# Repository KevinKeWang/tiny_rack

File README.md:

# tiny_rack
This is a V2 version of tiny_rack. With the release of the BambuLab H2D it's easy to print larger models. So I updated the eurorack case model for the 6U52HP, and the power board circuit for a more convenient and easy to use design. This version is closer to the aluminum eurorack case I sell. they are exactly the same in power and functionality. Now you can print your own 6U52hp eurorack case in any color you like!

**(tiny_rack v2)**

The first version is smaller and fits most 3D printers. If your printer cannot build such a large part, please browse the V1 version here: https://github.com/KevinKeWang/tiny_rack/tree/V1

**(tiny_rack v1)**

## Main features:

* One-piece 3D printed, no splicing, no metal rails required.
* Maximum current: +12V 2000mA, -12V 1000mA, +5V not available.
* Full load tested.
* The +12V and -12V output ripple is less than 100mV under all load conditions.
* Fully test powered by ZITAY D-Tap to DC(5.5 * 2.1 mm) Cable

## Portable scene using V-mount battery power supply
**Please note that the dtap output voltage should not be lower than 14.2V**
|  |  |
|------------------------------------------------|------------------------------------------------|

## Instructions
The main reason I started this project was the difficulty in finding a simple power bank solution when I was just starting out with DIY modulars. Most of the solutions required specialized rails. needed to control the precision otherwise the modulars would be difficult to install. there were many power board solutions but I couldn't be sure about the quality of their output. Some switching power supplies cause digital modulars to fail to boot.

This series contains the complete series of racks. and a power board with a decent quality of output. The racks is built entirely using 3D printing. one piece (including the rails) and simple to print. the screw holes are not threaded and need to be force screwed in using M3 screws to create the threads. this sacrifices the strength of the racks somewhat. but again makes the build very simple and ready to use straight after printing.

The power supply uses the original 7812/7912 LDO scheme. which is simple and reliable. and I've tested the ripple on the +/-12V rails to under 100mV under all load conditions. You can check the test report. it's not a perfect solution at the moment. but you can see exactly what kind of standards it can achieve.

**I no longer provide 5V in the power supply since most modulars that use 5V can be switched to convert 5V from 12V**

## 3D Print Instructions
* Be sure to place the model vertically, otherwise the dimensions will be off after printing, resulting in the modular not being installed.
* I have provided BambuStudio project files that can be used as a reference for the support structure. gcode files can be used directly for printing.
* Because different brands or different diameters of nozzles may produce different results when printing small circular holes. I made a screw hole diameter test model here. It is recommended to use this model to test before printing the modular case, and select the appropriate screw hole diameter to modify the plasticity source file. When I use the BambuLab H2D printer with a 0.4mm nozzle, a 2.5mm screw hole is the best size. If you use the same printer as me, you can directly use my gcode file for printing.

## Schematics and PCB

**Core PCB front side**

**Core PCB back side**

**How to connect two PCBs**

## Bill of materials (Core PCB)
| Designator                   | Qty | Value              | Footprint     | Description                    | Ref. Mouser                          | Ref. LCSC | References                            |
|------------------------------|-----|--------------------|---------------|--------------------------------|--------------------------------------|-----------|---------------------------------------|
| **SMT parts**                |     |                    |               |                                |                                      |           |                                       |
| LED1, LED2, LED3, LED4       | 4   | LED                | 0805          | LED                            | 638-1215UYCS530A28                   | C2987021  | EVERLIGHT 17-215/GHC-YP1Q2B16Y/3T     |
| R1, R2, R3, R5, R6, R10, R4  | 7   | 2.4k               | 0805          | Resistor                       | 667-ERJ-6ENF2401V                    | C17526    | UNI-ROYAL 0805W8F2401T5E              |
| R7, R8, R9                   | 3   | 510R               | 0805          | Resistor (Optional)            | 667-ERJ-6ENF5100V                    | C17734    | UNI-ROYAL 0805W8F5100T5E              |
| C4, C9                       | 2   | 100nF              | CASE-A-3216   | tantalum                       | 581-TAJA104K035                      | C7173     | Kyocera AVX TAJA104K035RNJ            |
| C3, C8                       | 2   | 330nF              | CASE-A-3216   | tantalum                       | 581-TAJA334K035                      | C8014     | Kyocera AVX TAJA334K035RNJ            |
| C11                          | 1   | 1uF                | CASE-A-3216   | tantalum                       | 581-TAJA105K035R                     | C7176     | Kyocera AVX TAJA105K035RNJ            |
| C10                          | 1   | 2.2uF              | CASE-B-3528   | tantalum                       | 581-TAJB225K035                      | C19276    | Kyocera AVX TAJB225K035RNJ            |
| D1, D2, D3                   | 3   | DIODE              | SMA(DO-214AC) | DIODE                          | 621-B360A-F                          | C94193    | DIODES B360A-13-F                     |
| **PTH parts**                |     |                    |               |                                |                                      |           |                                       |
| C2                           | 1   | 22uF               | D6.3xL7mm     | Electrolytic                   | 647-UKL1V220KEDANA                   | C433313   | Nichicon USV1V220MFD                  |
| C1                           | 1   | 120uF              | D8xL7mm       | Electrolytic                   | 667-50SEK120M                        | C3010233  | PANASONIC 50SEK120M                   |
| KK1, KK3, KK4                | 3   | Heat sink          |               | Heat sink                      | 532-529702B25G                       | C286227   | Heat sink                             |
| J1                           | 1   | DC Power Connector |               | 2.1 mm, 5.5 mm                 | 710-694106301002                     | C136744   | Wurth Elektronik 694106301002         |
| J2, J6                       | 2   | M3 screw terminal  |               | terminal (Optional)            | 534-7770                             | C481448   | Keystone 7770                         |
| **Adapter**                  |     |                    |               |                                |                                      |           |                                       |
| 15V Adapter                  | 1   | 15V Adapter        |               | GST60A15-P1J                   | 709-GST60A15-P1J                     | -         | MEANWELL 15V DC Adapter               |

**It is recommended to use the adapter model I have tested.**

## Bill of materials (EXP PCB)
| Designator                   | Qty | Value              | Footprint     | Description                    | Ref. Mouser                          | Ref. LCSC | References                            |
|------------------------------|-----|--------------------|---------------|--------------------------------|--------------------------------------|-----------|---------------------------------------|
| **SMT parts**                |     |                    |               |                                |                                      |           |                                       |
| J1, J2, J6, J7, J8, J9, J11, J12, J13, J14, J15, J16, J17, J18, J19, J20, J21, J22, J23, J24, J25, J26, J27, J28, J29, J30, J31, J32, J33, J34 | 30   | 2x8 header         | 2.54mm pitch  | 2x8 header                     | 710-61231620621                      | C2685064   | 2x8 male header, 2.54mm pitch         |
| J3, J4, J5, J10              | 4   | 2x3 header         | 2.54mm pitch  | 2x3 header                     | 710-61300621121                      | C358692   | 2x3 male header, 2.54mm pitch         |

## Mechanical assembly

**There is no circuit on the back of the expansion board, so it can be directly attached to any surface with tape.**

## Software

3D Modeling Software: plasticity

https://www.plasticity.xyz/

PCB Software: eagle

https://www.autodesk.com/products/eagle/overview

## Test Report
Test equipment:
* Gwinstek GPP-3323 DC Power Supply (as an electronic load) **for +12V -12V**
* Itech IT8500G+ DC Electronic Load **for +5V**
* Rigol MSO5000 Oscilloscopes **for ripple measurement**
* Software for automated testing
Test methods:
Each channel is cycled from 0mA to maximum load, 50mA in one step, to test all combinations of loads and output a CSV file.

**There are some power supply solutions that can generate large ripple or even fail in specific load scenarios, such as when the gap between positive and negative rail loads is too large. That's why my tests cover all load scenarios.**

## License
**The tiny_rack v2 project is made available under a CC-BY-NC-SA-3.0 license.**

If you want to make a few cases for your own use, go ahead and make them. If you're a synth studio and want to use them for product testing/demonstration etc, that's also welcome as long as it doesn't involve selling these case directly. **Please do not make and sell these case in bulk.**

## Links
Official website:  https://bitiworkshop.com/

Purchase here: https://store.bitiworkshop.com/

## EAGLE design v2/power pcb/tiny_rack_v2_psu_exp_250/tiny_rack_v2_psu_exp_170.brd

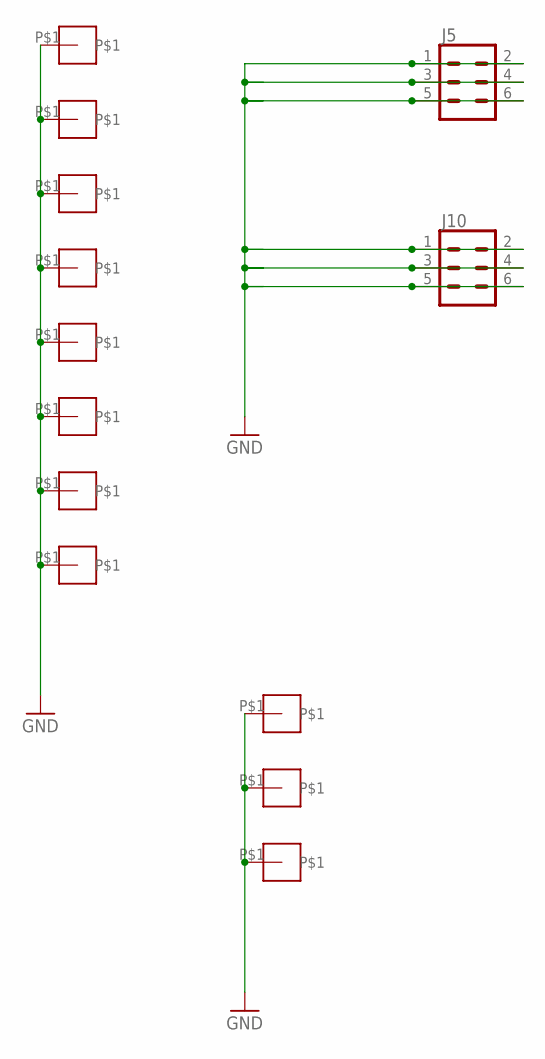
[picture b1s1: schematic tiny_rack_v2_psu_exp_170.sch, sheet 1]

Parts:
J5, J10: CONN_03X2FEMALE_SMD; 2X3_SMD
U$1, U$2, U$3, U$4, U$5, U$6, U$8, U$9, U$10, U$11, U$12: M3-HOLE

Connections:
GND: J5.1, J5.2, J5.3, J5.4, J5.5, J5.6, J10.1, J10.2, J10.3, J10.4, J10.5, J10.6, U$1.P$1, U$2.P$1, U$3.P$1, U$4.P$1, U$5.P$1, U$6.P$1, U$8.P$1, U$9.P$1, U$10.P$1, U$11.P$1, U$12.P$1; also elsewhere on the board

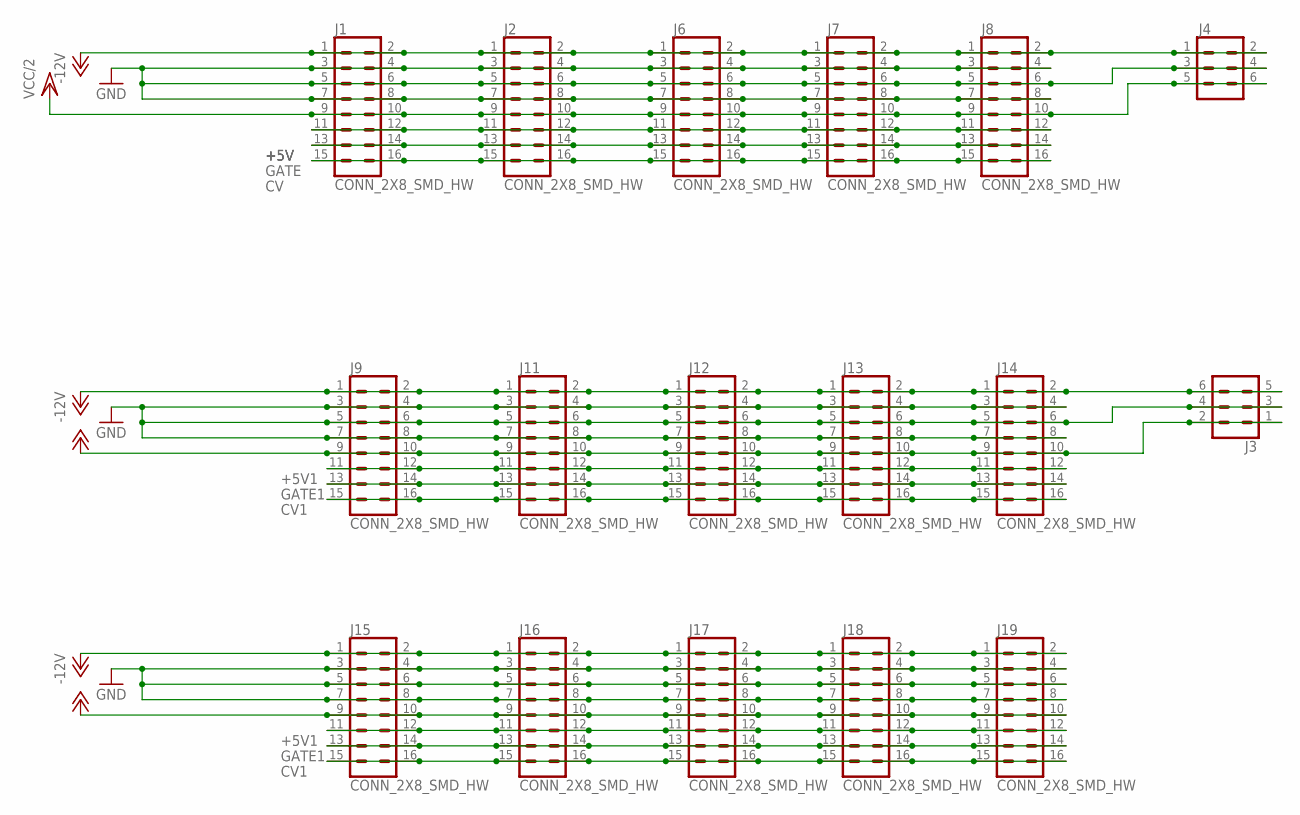
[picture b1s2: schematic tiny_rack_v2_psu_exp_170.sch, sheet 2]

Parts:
J1, J2, J6, J7, J8, J9, J11, J12, J13, J14, J15, J16, J17, J18, J19: CONN_2X8_SMD_HW; 2X8-SHROUDED_SMD_HW
J3, J4: CONN_03X2FEMALE_SMD; 2X3_SMD

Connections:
+5V: J1.11, J1.12, J2.11, J2.12, J6.11, J6.12, J7.11, J7.12, J8.11, J8.12; also elsewhere on the board
+5V1: J9.11, J9.12, J11.11, J11.12, J12.11, J12.12, J13.11, J13.12, J14.11, J14.12, J15.11, J15.12, J16.11, J16.12, J17.11, J17.12, J18.11, J18.12, J19.11, J19.12; also elsewhere on the board
+12V: J3.1, J3.2, J9.9, J9.10, J11.9, J11.10, J12.9, J12.10, J13.9, J13.10, J14.9, J14.10, J15.9, J15.10, J16.9, J16.10, J17.9, J17.10, J18.9, J18.10, J19.9, J19.10; also elsewhere on the board
-12V: J1.1, J1.2, J2.1, J2.2, J3.5, J3.6, J4.1, J4.2, J6.1, J6.2, J7.1, J7.2, J8.1, J8.2, J9.1, J9.2, J11.1, J11.2, J12.1, J12.2, J13.1, J13.2, J14.1, J14.2, J15.1, J15.2, J16.1, J16.2, J17.1, J17.2, J18.1, J18.2, J19.1, J19.2; also elsewhere on the board
CV: J1.15, J1.16, J2.15, J2.16, J6.15, J6.16, J7.15, J7.16, J8.15, J8.16; also elsewhere on the board
CV1: J9.15, J9.16, J11.15, J11.16, J12.15, J12.16, J13.15, J13.16, J14.15, J14.16, J15.15, J15.16, J16.15, J16.16, J17.15, J17.16, J18.15, J18.16, J19.15, J19.16; also elsewhere on the board
GATE: J1.13, J1.14, J2.13, J2.14, J6.13, J6.14, J7.13, J7.14, J8.13, J8.14; also elsewhere on the board
GATE1: J9.13, J9.14, J11.13, J11.14, J12.13, J12.14, J13.13, J13.14, J14.13, J14.14, J15.13, J15.14, J16.13, J16.14, J17.13, J17.14, J18.13, J18.14, J19.13, J19.14; also elsewhere on the board
GND: J1.3, J1.4, J1.5, J1.6, J1.7, J1.8, J2.3, J2.4, J2.5, J2.6, J2.7, J2.8, J3.3, J3.4, J4.3, J4.4, J6.3, J6.4, J6.5, J6.6, J6.7, J6.8, J7.3, J7.4, J7.5, J7.6, J7.7, J7.8, J8.3, J8.4, J8.5, J8.6, J8.7, J8.8, J9.3, J9.4, J9.5, J9.6, J9.7, J9.8, J11.3, J11.4, J11.5, J11.6, J11.7, J11.8, J12.3, J12.4, J12.5, J12.6, J12.7, J12.8, J13.3, J13.4, J13.5, J13.6, J13.7, J13.8, J14.3, J14.4, J14.5, J14.6, J14.7, J14.8, J15.3, J15.4, J15.5, J15.6, J15.7, J15.8, J16.3, J16.4, J16.5, J16.6, J16.7, J16.8, J17.3, J17.4, J17.5, J17.6, J17.7, J17.8, J18.3, J18.4, J18.5, J18.6, J18.7, J18.8, J19.3, J19.4, J19.5, J19.6, J19.7, J19.8; also elsewhere on the board
VCC/2: J1.9, J1.10, J2.9, J2.10, J4.5, J4.6, J6.9, J6.10, J7.9, J7.10, J8.9, J8.10; also elsewhere on the board

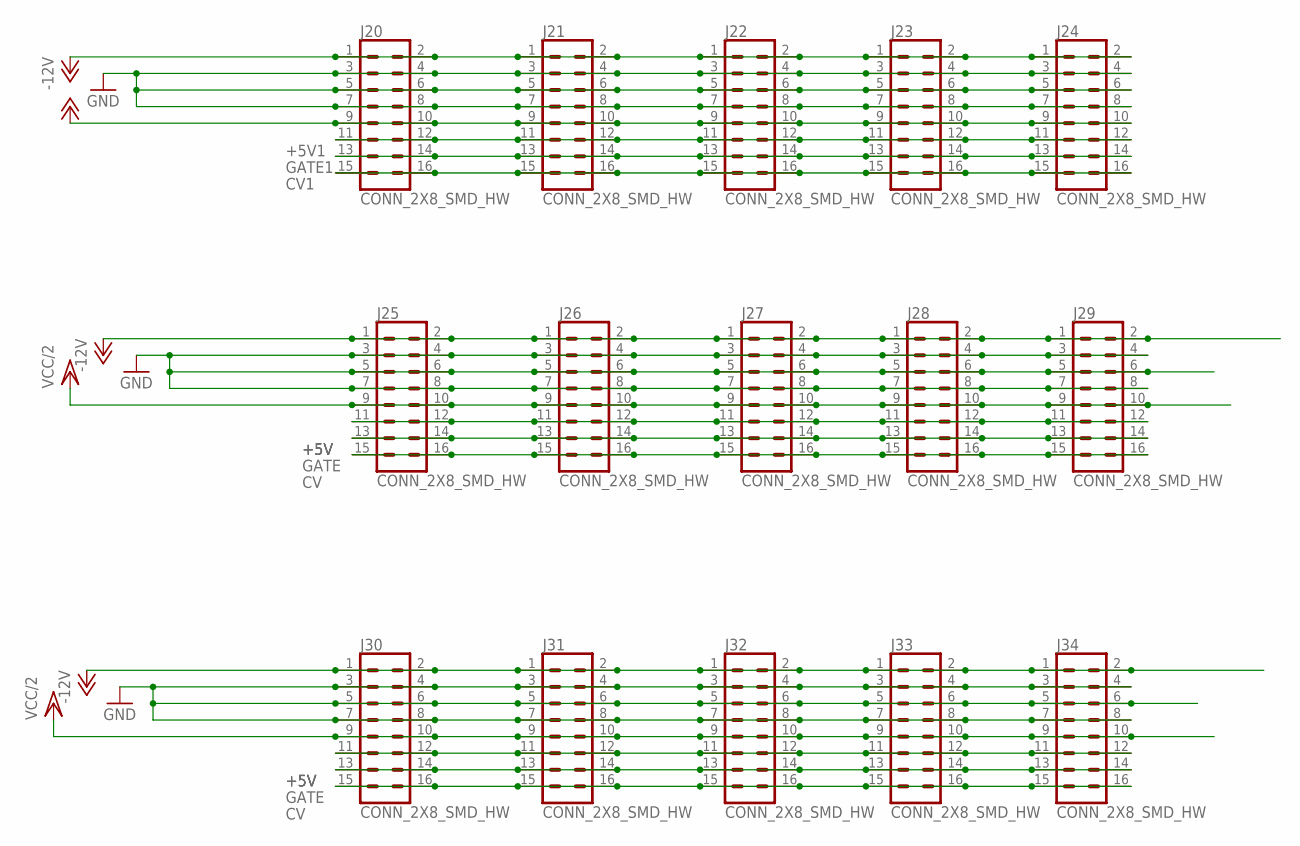
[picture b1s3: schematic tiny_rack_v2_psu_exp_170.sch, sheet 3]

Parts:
J20, J21, J22, J23, J24, J25, J26, J27, J28, J29, J30, J31, J32, J33, J34: CONN_2X8_SMD_HW; 2X8-SHROUDED_SMD_HW

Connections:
+5V: J25.11, J25.12, J26.11, J26.12, J27.11, J27.12, J28.11, J28.12, J29.11, J29.12, J30.11, J30.12, J31.11, J31.12, J32.11, J32.12, J33.11, J33.12, J34.11, J34.12; also elsewhere on the board
+5V1: J20.11, J20.12, J21.11, J21.12, J22.11, J22.12, J23.11, J23.12, J24.11, J24.12; also elsewhere on the board
+12V: J20.9, J20.10, J21.9, J21.10, J22.9, J22.10, J23.9, J23.10, J24.9, J24.10; also elsewhere on the board
-12V: J20.1, J20.2, J21.1, J21.2, J22.1, J22.2, J23.1, J23.2, J24.1, J24.2, J25.1, J25.2, J26.1, J26.2, J27.1, J27.2, J28.1, J28.2, J29.1, J29.2, J30.1, J30.2, J31.1, J31.2, J32.1, J32.2, J33.1, J33.2, J34.1, J34.2; also elsewhere on the board
CV: J25.15, J25.16, J26.15, J26.16, J27.15, J27.16, J28.15, J28.16, J29.15, J29.16, J30.15, J30.16, J31.15, J31.16, J32.15, J32.16, J33.15, J33.16, J34.15, J34.16; also elsewhere on the board
CV1: J20.15, J20.16, J21.15, J21.16, J22.15, J22.16, J23.15, J23.16, J24.15, J24.16; also elsewhere on the board
GATE: J25.13, J25.14, J26.13, J26.14, J27.13, J27.14, J28.13, J28.14, J29.13, J29.14, J30.13, J30.14, J31.13, J31.14, J32.13, J32.14, J33.13, J33.14, J34.13, J34.14; also elsewhere on the board
GATE1: J20.13, J20.14, J21.13, J21.14, J22.13, J22.14, J23.13, J23.14, J24.13, J24.14; also elsewhere on the board
GND: J20.3, J20.4, J20.5, J20.6, J20.7, J20.8, J21.3, J21.4, J21.5, J21.6, J21.7, J21.8, J22.3, J22.4, J22.5, J22.6, J22.7, J22.8, J23.3, J23.4, J23.5, J23.6, J23.7, J23.8, J24.3, J24.4, J24.5, J24.6, J24.7, J24.8, J25.3, J25.4, J25.5, J25.6, J25.7, J25.8, J26.3, J26.4, J26.5, J26.6, J26.7, J26.8, J27.3, J27.4, J27.5, J27.6, J27.7, J27.8, J28.3, J28.4, J28.5, J28.6, J28.7, J28.8, J29.3, J29.4, J29.5, J29.6, J29.7, J29.8, J30.3, J30.4, J30.5, J30.6, J30.7, J30.8, J31.3, J31.4, J31.5, J31.6, J31.7, J31.8, J32.3, J32.4, J32.5, J32.6, J32.7, J32.8, J33.3, J33.4, J33.5, J33.6, J33.7, J33.8, J34.3, J34.4, J34.5, J34.6, J34.7, J34.8; also elsewhere on the board
VCC/2: J25.9, J25.10, J26.9, J26.10, J27.9, J27.10, J28.9, J28.10, J29.9, J29.10, J30.9, J30.10, J31.9, J31.10, J32.9, J32.10, J33.9, J33.10, J34.9, J34.10; also elsewhere on the board

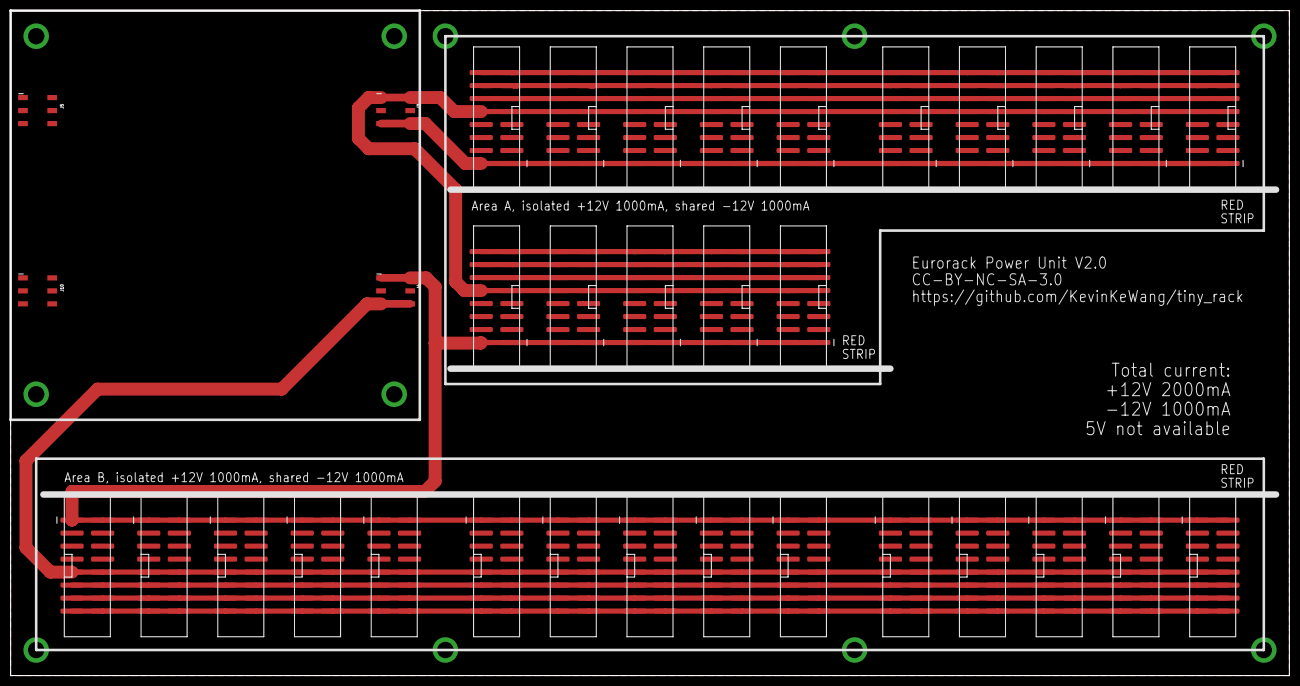
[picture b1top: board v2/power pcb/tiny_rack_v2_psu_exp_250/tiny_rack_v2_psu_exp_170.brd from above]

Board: 4 copper layers, 250.0 x 130.0 mm, 45 parts (0 on the bottom side), 10 nets.

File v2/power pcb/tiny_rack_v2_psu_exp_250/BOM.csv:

Designator,Comment,Footprint,JLC PartNo.
"J3, J4, J5, J10",2X3PIN,SMT,C780054
"J1, J2, J6, J7, J8, J9, J11, J12, J13, J14, J15, J16, J17, J18, J19, J20, J21, J22, J23, J24, J25, J26, J27, J28, J29, J30, J31, J32, J33, J34",2X8PIN,SMT,C2685064

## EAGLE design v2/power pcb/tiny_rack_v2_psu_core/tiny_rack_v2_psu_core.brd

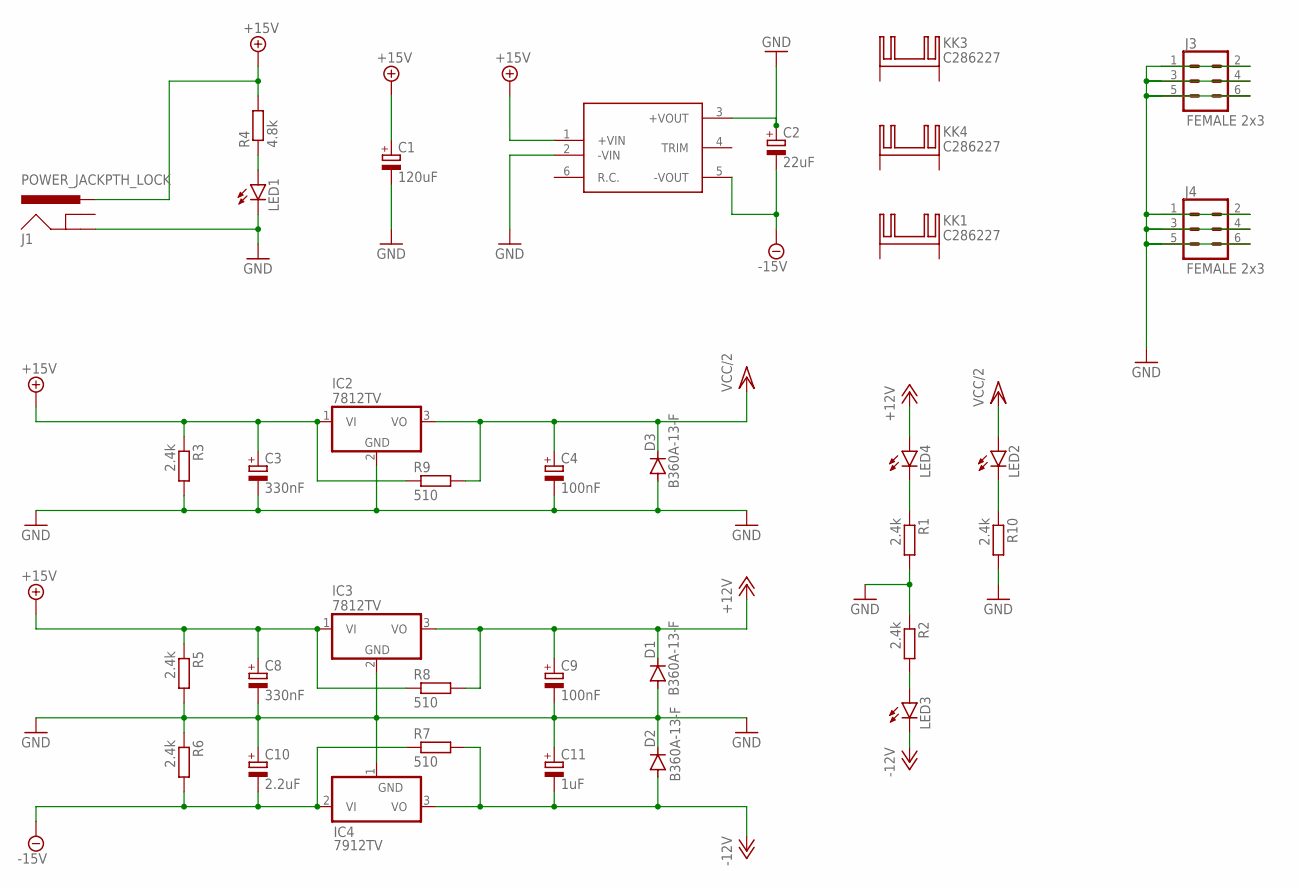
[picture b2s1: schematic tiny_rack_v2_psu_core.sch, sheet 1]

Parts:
C1: 120uF; E5-10,5
C2: 22uF; E2,5-6
C3, C8: 330nF; CAPMP3216X180N
C4, C9: 100nF; CAPMP3216X180N
C10: 2.2uF; CAPMP3528X210N
C11: 1uF; CAPMP3216X180N
D1, D2, D3: B360A-13-F; DO-214AC
IC1: SKMW
IC2, IC3: 7812TV; TO220V
IC4: 7912TV; TO220V
J1: POWER_JACKPTH_LOCK; POWER_JACK_PTH_LOCK
J3, J4: FEMALE 2x3; 2X3
KK1, KK3, KK4: C286227
LED1, LED2, LED3, LED4: LEDCHIP-LED0805; CHIP-LED0805
R1, R2, R3, R5, R6, R10: 2.4k; R0805
R4: 4.8k; R0805
R7, R8, R9: 510; R0805

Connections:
+12V: C9.1 (+), D1.C, IC3.3 (VO), LED4.A, R8.2; also elsewhere on the board
+15V: C1.+, C3.1 (+), C8.1 (+), IC1.1 (+VIN), IC2.1 (VI), IC3.1 (VI), J1.PWR, R3.1, R4.2, R5.1, R8.1, R9.1; also elsewhere on the board
-12V: C11.2 (-), D2.A, IC4.3 (VO), LED3.C, R7.2; also elsewhere on the board
-15V: C2.-, C10.2 (-), IC1.5 (-VOUT), IC4.2 (VI), R6.2, R7.1
GND: C1.-, C2.+, C3.2 (-), C4.2 (-), C8.2 (-), C9.2 (-), C10.1 (+), C11.1 (+), D1.A, D2.C, D3.A, IC1.2 (-VIN), IC1.3 (+VOUT), IC2.2 (GND), IC3.2 (GND), IC4.1 (GND), J1.GND, J3.1, J3.2, J3.3, J3.4, J3.5, J3.6, J4.1, J4.2, J4.3, J4.4, J4.5, J4.6, LED1.C, R1.2, R2.1, R3.2, R5.2, R6.1, R10.2; also elsewhere on the board
unnamed: LED4.C, R1.1
unnamed: LED2.C, R10.1
unnamed: LED3.A, R2.2
unnamed: LED1.A, R4.1
VCC/2: C4.1 (+), D3.C, IC2.3 (VO), LED2.A, R9.2; also elsewhere on the board

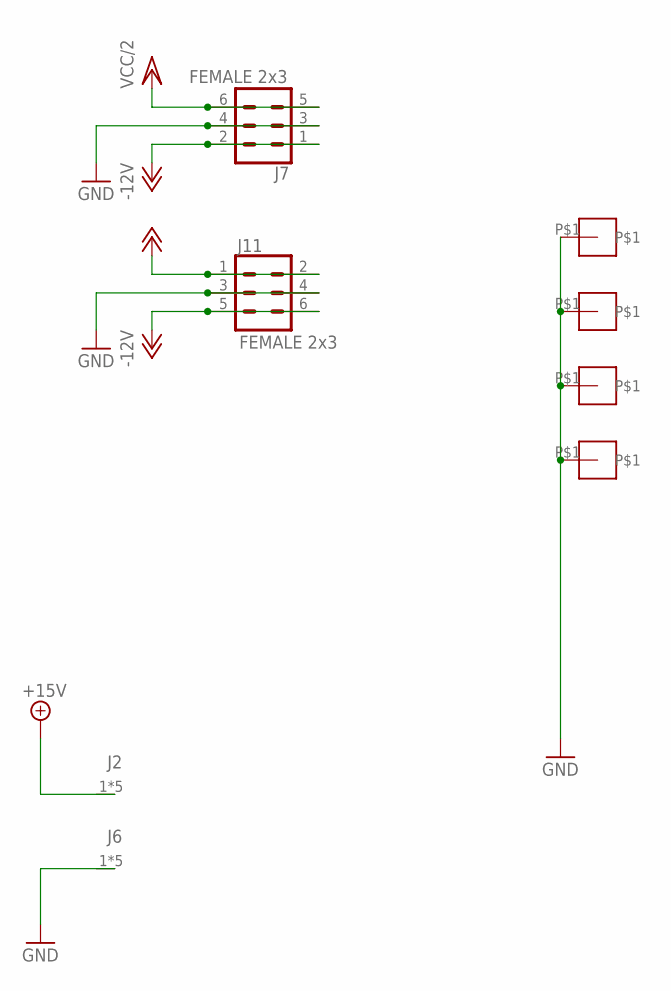
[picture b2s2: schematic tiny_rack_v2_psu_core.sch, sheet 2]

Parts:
J2, J6: 30A-SCREW-CONN; 50X72
J7, J11: FEMALE 2x3; 2X3
U$3, U$4, U$5, U$6: M3-HOLE

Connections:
+12V: J11.1, J11.2; also elsewhere on the board
+15V: J2.1, J2.2, J2.3, J2.4, J2.P$1; also elsewhere on the board
-12V: J7.1, J7.2, J11.5, J11.6; also elsewhere on the board
GND: J6.1, J6.2, J6.3, J6.4, J6.P$1, J7.3, J7.4, J11.3, J11.4, U$3.P$1, U$4.P$1, U$5.P$1, U$6.P$1; also elsewhere on the board
VCC/2: J7.5, J7.6; also elsewhere on the board

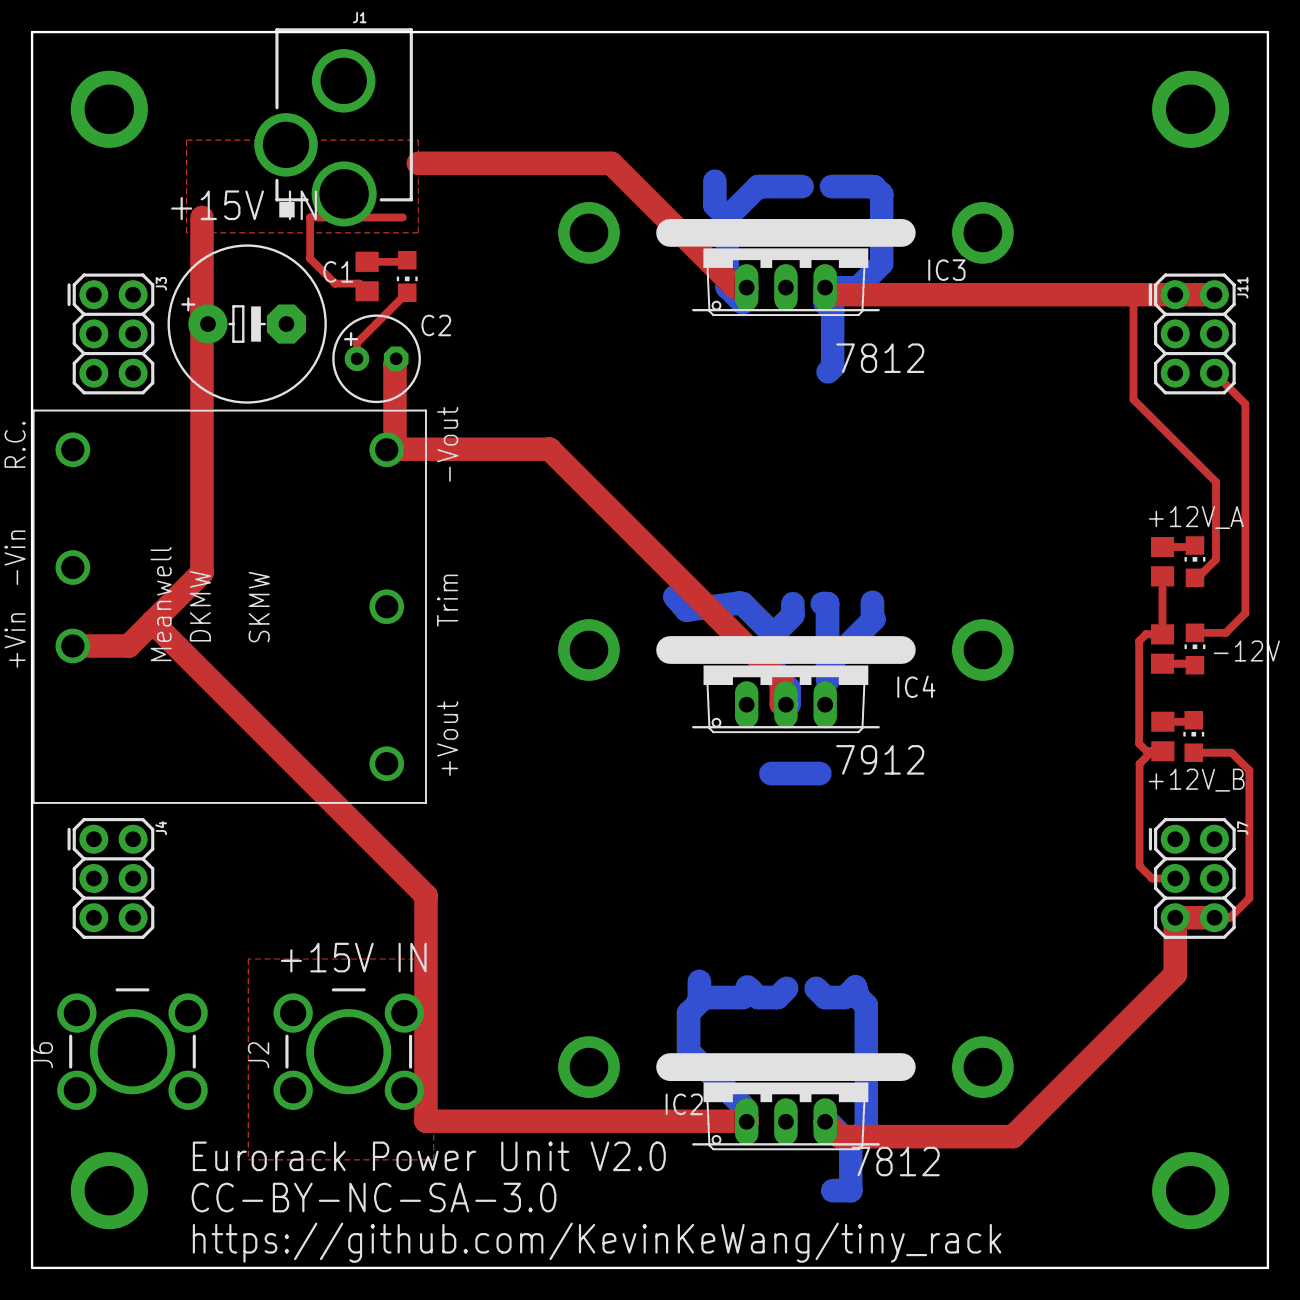
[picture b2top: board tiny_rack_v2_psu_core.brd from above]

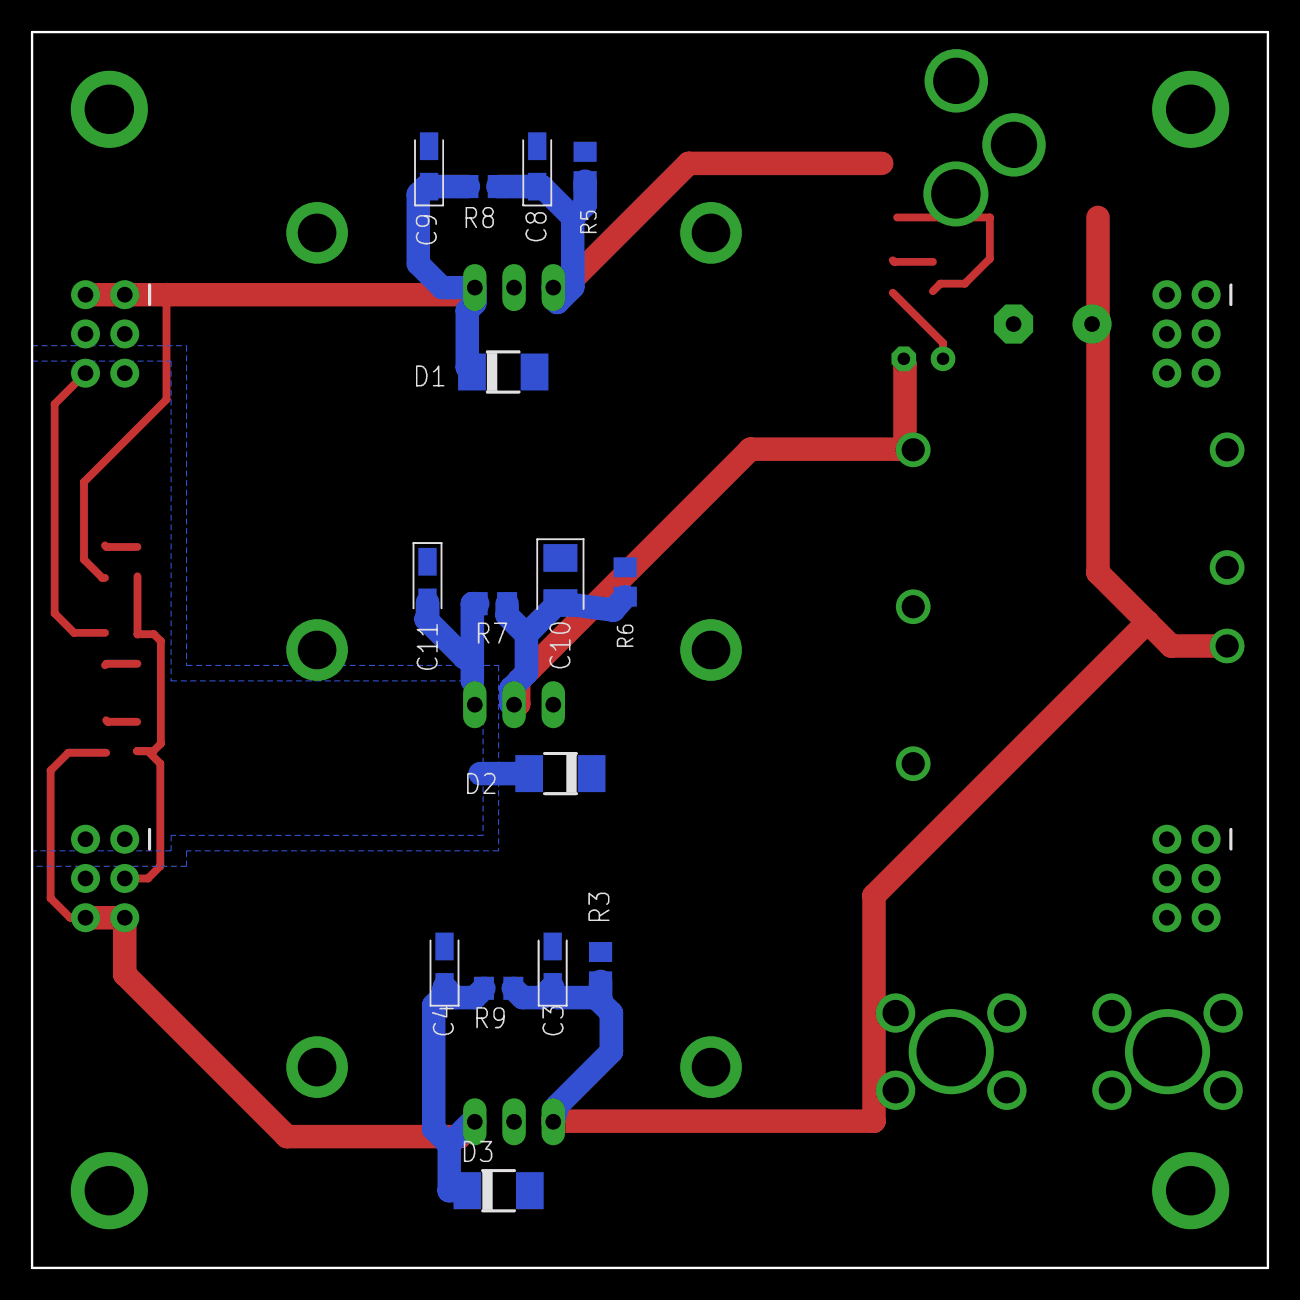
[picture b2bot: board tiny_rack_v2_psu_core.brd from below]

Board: 4 copper layers, 80.0 x 80.0 mm, 43 parts (15 on the bottom side), 10 nets.

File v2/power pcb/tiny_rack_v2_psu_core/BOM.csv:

Designator,Qty,Comment,Footprint,JLC PartNo.
"LED1, LED2, LED3, LED4",4,LED,0805,C389524
"C4, C9",2,100nF,C7173,C7173
C1,1,120uF,C134861,C134861
C11,1,1uF,C7176,C7176
C10,1,2.2uF,C19276,C19276
"R1, R2, R3, R5, R6, R10, R4",7,2.4k,0805,C17526
C2,1,22uF,C1578600,C1578600
"J2, J6, J8, J9",4,30A-SCREW-CONN,50X72,C481448
"C3, C8",2,330nF,C8014,C8014
"R7, R8, R9",3,510R,0805,C17734
"D1, D2, D3",3,B360A-13-F,DO-214AC,C94193
"KK1, KK3, KK4",3,C286227,C286227,C286227
J1,1,C136744,C136744,C136744

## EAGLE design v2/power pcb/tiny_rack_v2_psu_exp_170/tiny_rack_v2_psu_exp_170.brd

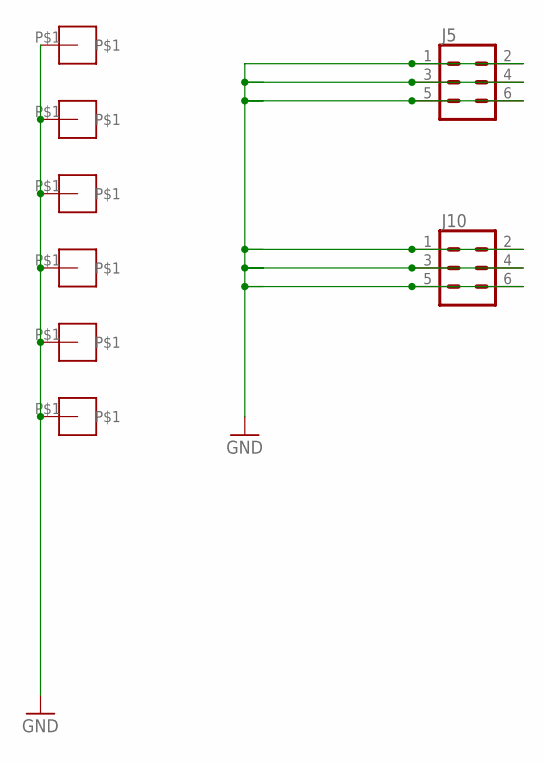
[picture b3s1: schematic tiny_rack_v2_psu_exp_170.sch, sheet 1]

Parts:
J5, J10: CONN_03X2FEMALE_SMD; 2X3_SMD
U$1, U$2, U$3, U$4, U$5, U$6: M3-HOLE

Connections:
GND: J5.1, J5.2, J5.3, J5.4, J5.5, J5.6, J10.1, J10.2, J10.3, J10.4, J10.5, J10.6, U$1.P$1, U$2.P$1, U$3.P$1, U$4.P$1, U$5.P$1, U$6.P$1; also elsewhere on the board

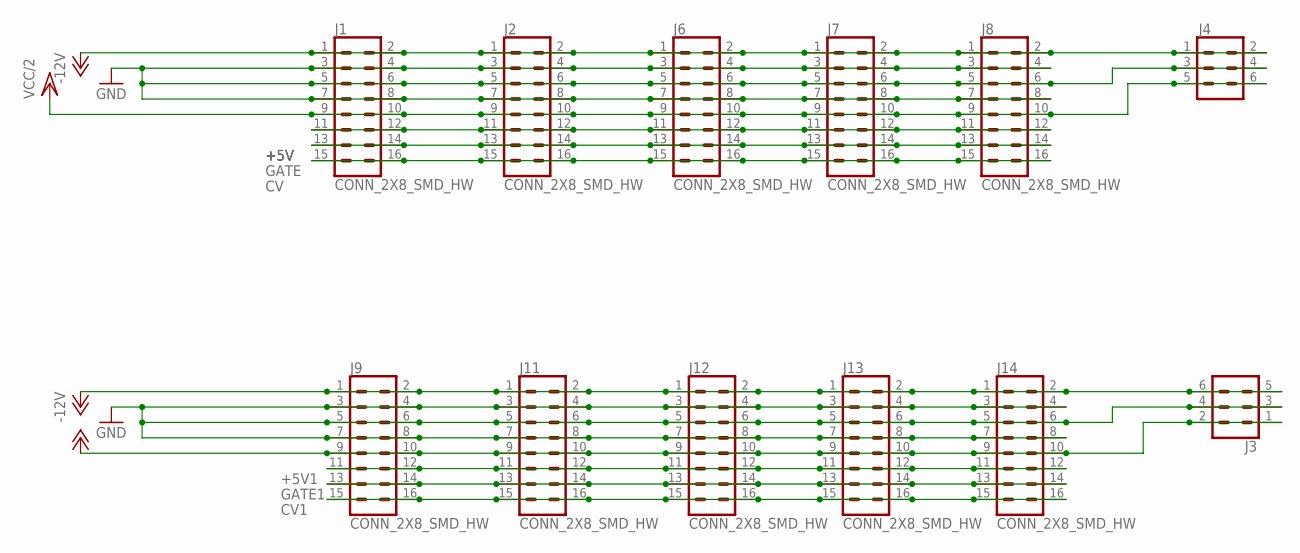
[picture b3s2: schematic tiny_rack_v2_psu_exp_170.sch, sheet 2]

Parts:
J1, J2, J6, J7, J8, J9, J11, J12, J13, J14: CONN_2X8_SMD_HW; 2X8-SHROUDED_SMD_HW
J3, J4: CONN_03X2FEMALE_SMD; 2X3_SMD

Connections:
+5V: J1.11, J1.12, J2.11, J2.12, J6.11, J6.12, J7.11, J7.12, J8.11, J8.12
+5V1: J9.11, J9.12, J11.11, J11.12, J12.11, J12.12, J13.11, J13.12, J14.11, J14.12
+12V: J3.1, J3.2, J9.9, J9.10, J11.9, J11.10, J12.9, J12.10, J13.9, J13.10, J14.9, J14.10
-12V: J1.1, J1.2, J2.1, J2.2, J3.5, J3.6, J4.1, J4.2, J6.1, J6.2, J7.1, J7.2, J8.1, J8.2, J9.1, J9.2, J11.1, J11.2, J12.1, J12.2, J13.1, J13.2, J14.1, J14.2
CV: J1.15, J1.16, J2.15, J2.16, J6.15, J6.16, J7.15, J7.16, J8.15, J8.16
CV1: J9.15, J9.16, J11.15, J11.16, J12.15, J12.16, J13.15, J13.16, J14.15, J14.16
GATE: J1.13, J1.14, J2.13, J2.14, J6.13, J6.14, J7.13, J7.14, J8.13, J8.14
GATE1: J9.13, J9.14, J11.13, J11.14, J12.13, J12.14, J13.13, J13.14, J14.13, J14.14
GND: J1.3, J1.4, J1.5, J1.6, J1.7, J1.8, J2.3, J2.4, J2.5, J2.6, J2.7, J2.8, J3.3, J3.4, J4.3, J4.4, J6.3, J6.4, J6.5, J6.6, J6.7, J6.8, J7.3, J7.4, J7.5, J7.6, J7.7, J7.8, J8.3, J8.4, J8.5, J8.6, J8.7, J8.8, J9.3, J9.4, J9.5, J9.6, J9.7, J9.8, J11.3, J11.4, J11.5, J11.6, J11.7, J11.8, J12.3, J12.4, J12.5, J12.6, J12.7, J12.8, J13.3, J13.4, J13.5, J13.6, J13.7, J13.8, J14.3, J14.4, J14.5, J14.6, J14.7, J14.8; also elsewhere on the board
VCC/2: J1.9, J1.10, J2.9, J2.10, J4.5, J4.6, J6.9, J6.10, J7.9, J7.10, J8.9, J8.10

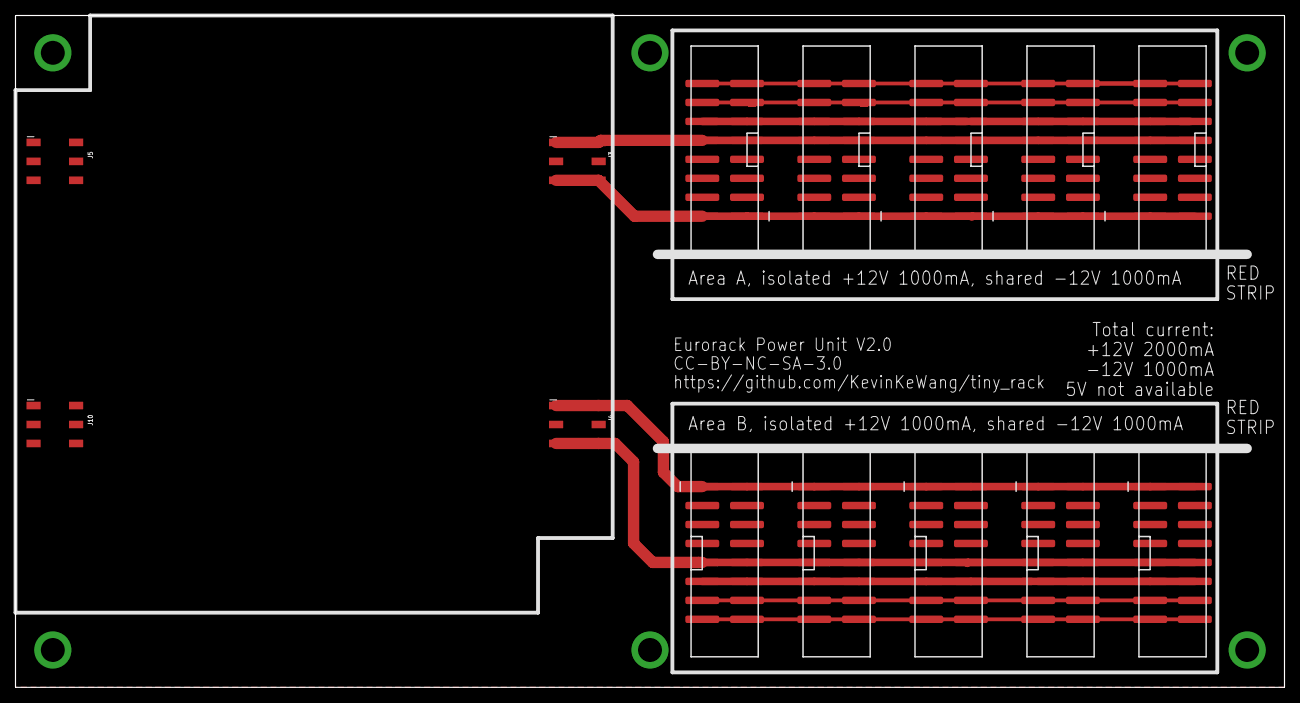
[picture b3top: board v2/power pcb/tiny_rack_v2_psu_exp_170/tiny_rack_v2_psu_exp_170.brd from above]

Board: 4 copper layers, 170.0 x 90.0 mm, 20 parts (0 on the bottom side), 10 nets.

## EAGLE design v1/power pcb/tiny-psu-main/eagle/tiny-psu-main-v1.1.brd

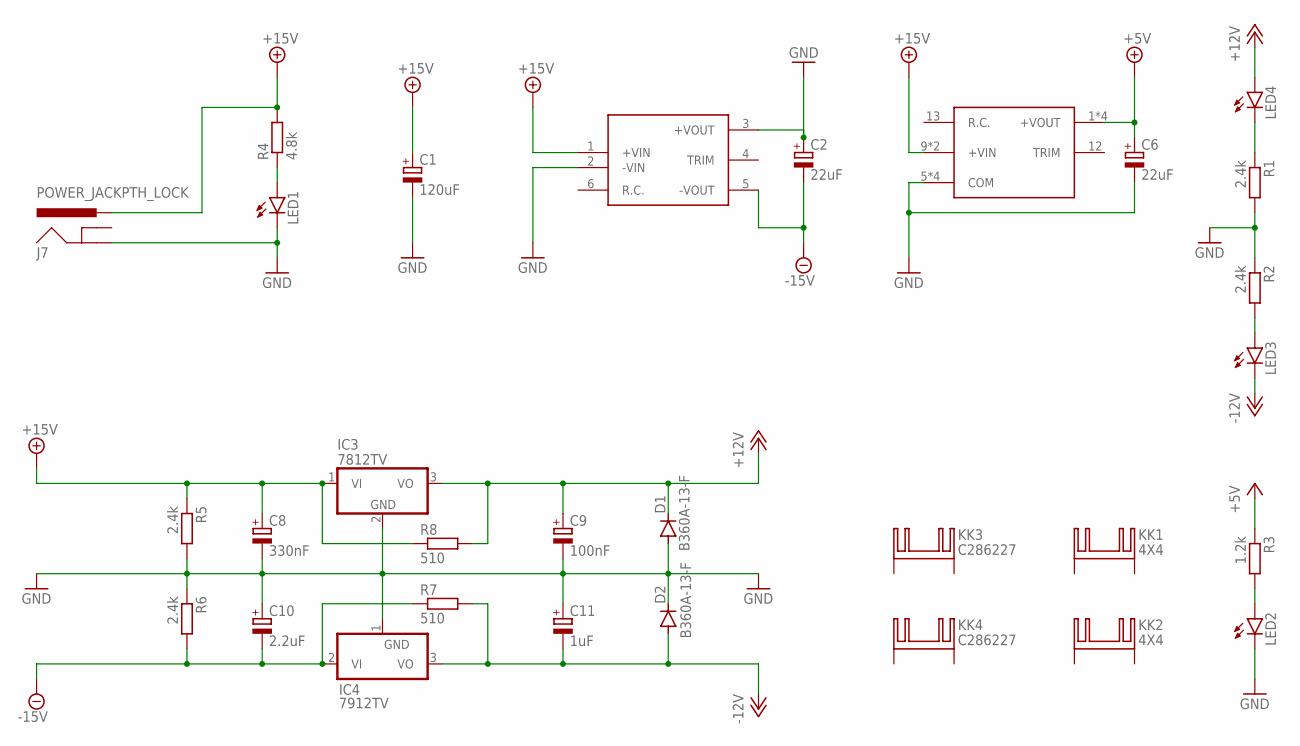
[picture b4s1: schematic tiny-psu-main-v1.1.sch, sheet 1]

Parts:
C1: 120uF; E5-10,5
C2, C6: 22uF; E2,5-6
C8: 330nF; CAPMP3216X180N
C9: 100nF; CAPMP3216X180N
C10: 2.2uF; CAPMP3528X210N
C11: 1uF; CAPMP3216X180N
D1, D2: B360A-13-F; DO-214AC
IC1: SKMW
IC2: NID100-5; NID65-HORIZONTAL
IC3: 7812TV; TO220V
IC4: 7912TV; TO220V
J7: POWER_JACKPTH_LOCK; POWER_JACK_PTH_LOCK
KK1, KK2: 4X4
KK3, KK4: C286227
LED1, LED2, LED3, LED4: LEDCHIP-LED0805; CHIP-LED0805
R1, R2, R5, R6: 2.4k; R0805
R3: 1.2k; R0805
R4: 4.8k; R0805
R7, R8: 510; R0805

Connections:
+5V: C6.+, IC2.1 (+VOUT), IC2.2 (+VOUT), IC2.3 (+VOUT), IC2.4 (+VOUT), R3.1; also elsewhere on the board
+12V: C9.1 (+), D1.C, IC3.3 (VO), LED4.A, R8.2; also elsewhere on the board
+15V: C1.+, C8.1 (+), IC1.1 (+VIN), IC2.9 (+VIN), IC2.10 (+VIN), IC3.1 (VI), J7.PWR, R4.2, R5.1, R8.1
-12V: C11.2 (-), D2.A, IC4.3 (VO), LED3.C, R7.2; also elsewhere on the board
-15V: C2.-, C10.2 (-), IC1.5 (-VOUT), IC4.2 (VI), R6.2, R7.1
GND: C1.-, C2.+, C6.-, C8.2 (-), C9.2 (-), C10.1 (+), C11.1 (+), D1.A, D2.C, IC1.2 (-VIN), IC1.3 (+VOUT), IC2.5 (COM), IC2.6 (COM), IC2.7 (COM), IC2.8 (COM), IC3.2 (GND), IC4.1 (GND), J7.GND, LED1.C, LED2.C, R1.2, R2.1, R5.2, R6.1; also elsewhere on the board
unnamed: LED4.C, R1.1
unnamed: LED3.A, R2.2
unnamed: LED1.A, R4.1
unnamed: LED2.A, R3.2

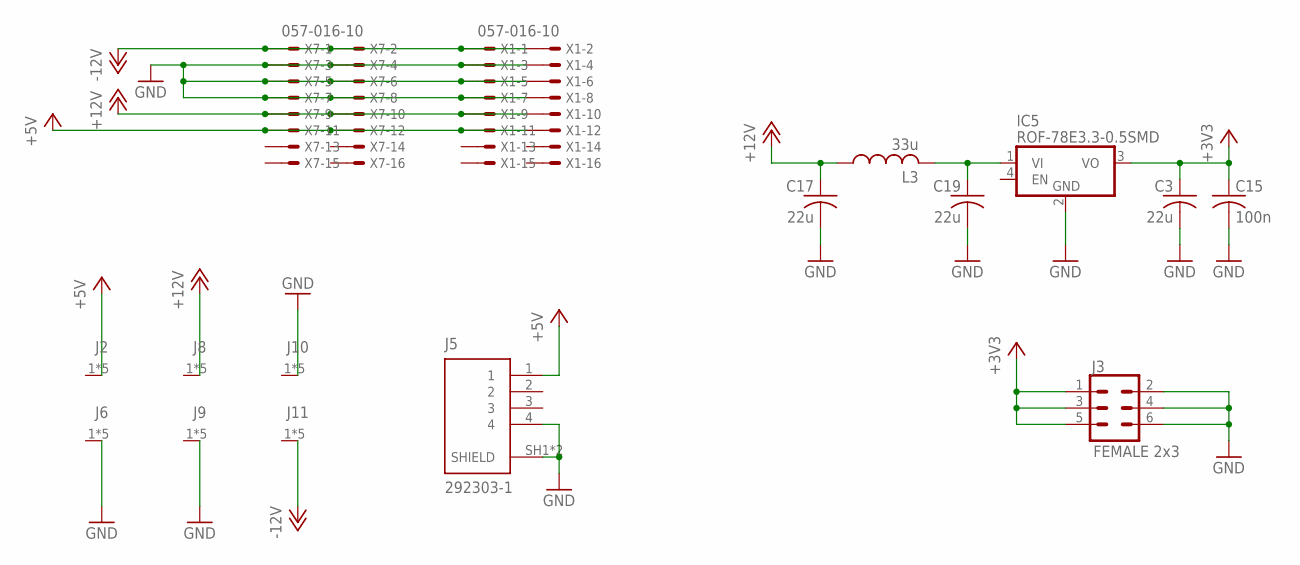
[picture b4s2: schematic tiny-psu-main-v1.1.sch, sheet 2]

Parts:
C3, C17, C19: 22u; C1206
C15: 100n; C0402
IC5: ROF-78E3.3-0.5SMD; ROF78EXX-0.5SMD
J2, J6, J8, J9, J10, J11: 30A-SCREW-CONN; 50X72
J3: FEMALE 2x3; 2X3
J5: 292303-1
L3: 33u; L2012C
X1, X7: 057-016-10; 057-016-1

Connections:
+3V3: C3.1, C15.1, IC5.3 (VO), J3.1, J3.3, J3.5
+5V: J2.1, J2.2, J2.3, J2.4, J2.P$1, J5.1, X1.11, X1.12, X7.11, X7.12; also elsewhere on the board
+12V: C17.1, J8.1, J8.2, J8.3, J8.4, J8.P$1, L3.1, X1.9, X1.10, X7.9, X7.10; also elsewhere on the board
-12V: J11.1, J11.2, J11.3, J11.4, J11.P$1, X1.1, X1.2, X7.1, X7.2; also elsewhere on the board
GND: C3.2, C15.2, C17.2, C19.2, IC5.2 (GND), J3.2, J3.4, J3.6, J5.4, J5.SH1 (SHIELD), J5.SH2 (SHIELD), J6.1, J6.2, J6.3, J6.4, J6.P$1, J9.1, J9.2, J9.3, J9.4, J9.P$1, J10.1, J10.2, J10.3, J10.4, J10.P$1, X1.3, X1.4, X1.5, X1.6, X1.7, X1.8, X7.3, X7.4, X7.5, X7.6, X7.7, X7.8; also elsewhere on the board
unnamed: C19.1, IC5.1 (VI), L3.2

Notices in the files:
v1/power pcb/tiny-psu-exp/eagle/tiny-psu-exp-v1.1.brd:
cc-by-sa KevinKeWang 2023
parts and their libraries:
SparkFun-Connectors: Licensing: Creative Commons ShareAlike 4.0 International - https://creativecommons.org/licenses/by-sa/4.0
